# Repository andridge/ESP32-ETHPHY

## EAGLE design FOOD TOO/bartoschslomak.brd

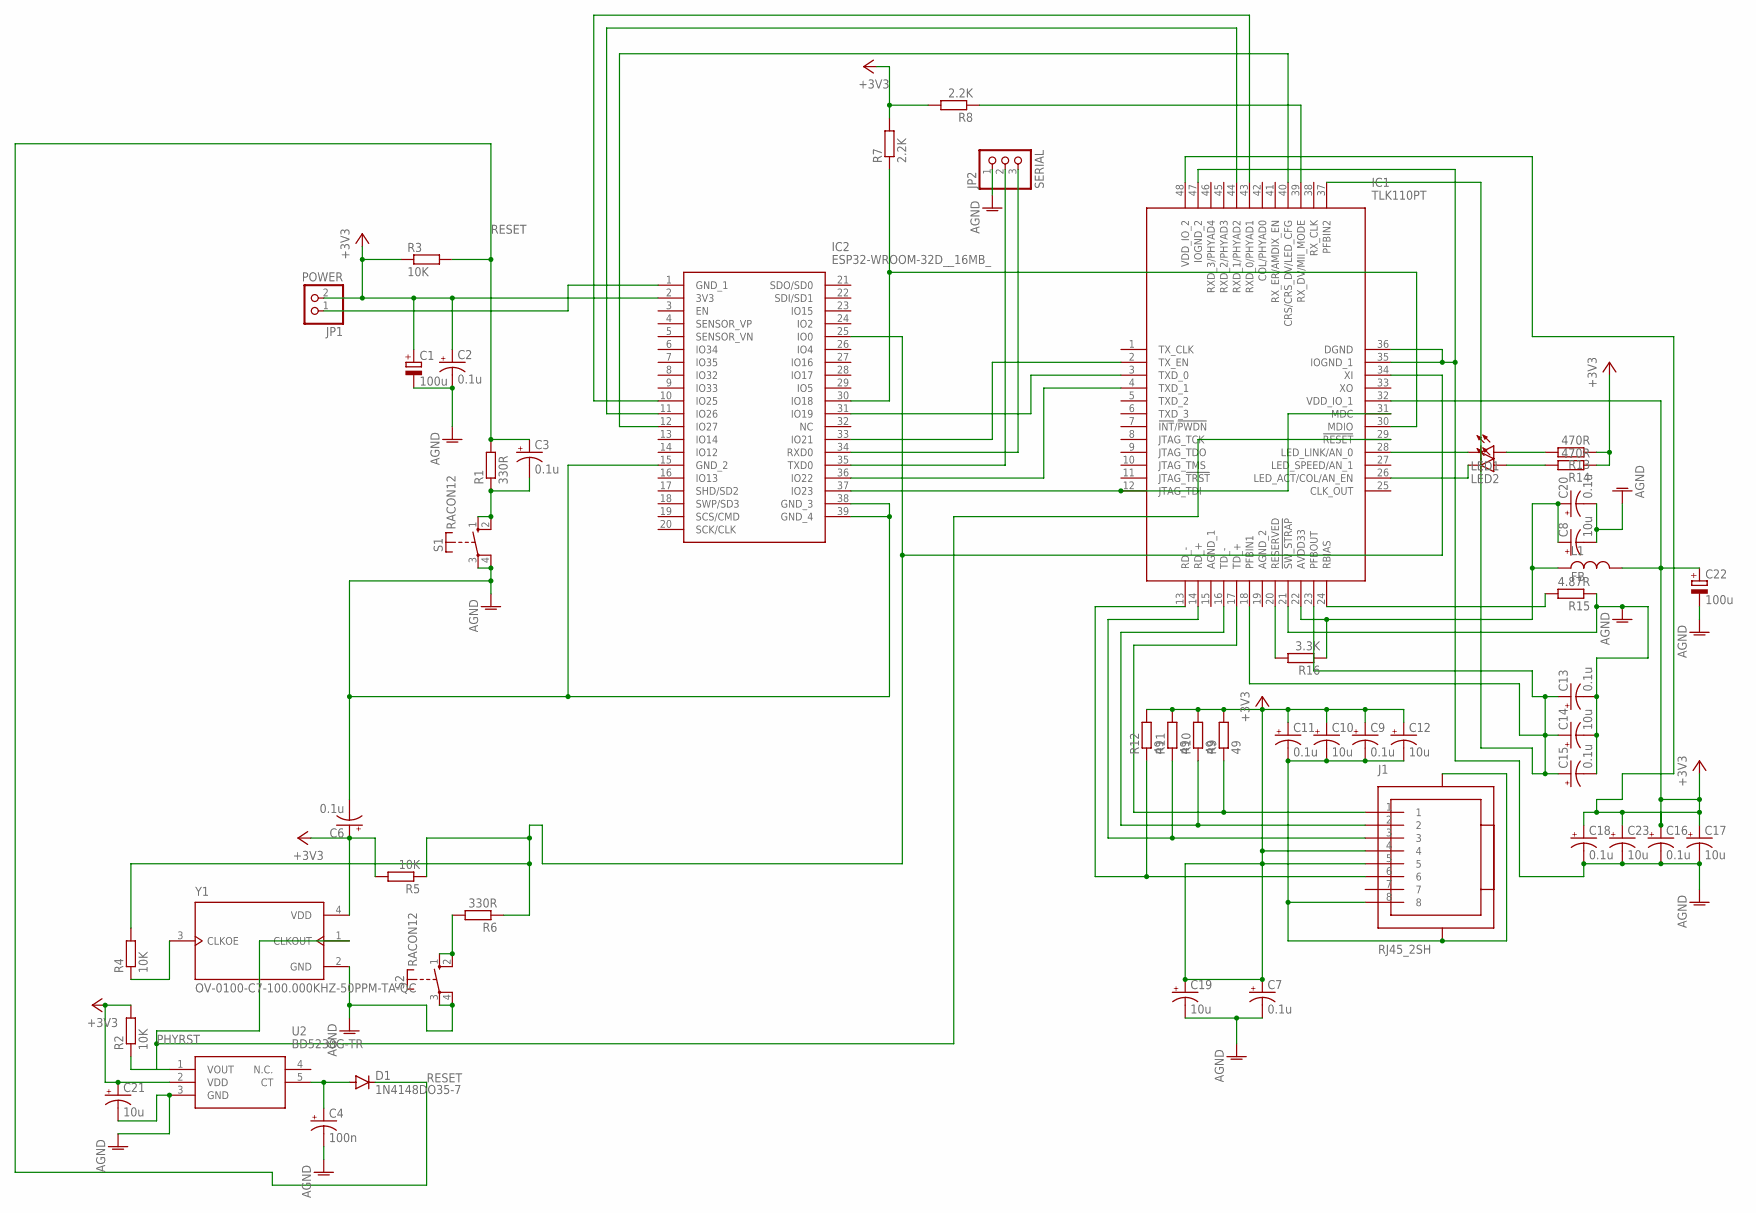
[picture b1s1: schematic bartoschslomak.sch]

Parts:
C1, C22: 100u; TT2D7
C2, C3, C6, C7, C9, C11, C13, C15, C16, C18, C20: 0.1u; A/3216-18R
C4: 100n; A/3216-18R
C8, C10, C12, C14, C17, C19, C21, C23: 10u; A/3216-18R
D1: 1N4148DO35-7; DO35-7
IC1: TLK110PT; QFP50P900X900X160-48N
IC2: ESP32-WROOM-32D__16MB_; ESP32WROOM32D16MB
J1: RJ45_2SH; RJ45_LP_RA_SMT
JP1: POWER; 1X02
JP2: SERIAL; 1X03
LED1, LED2: LED; SMARTLED-TTW
R1, R6: 330R; R01005
R2, R3, R4, R5: 10K; R01005
R7, R8: 2.2K; R01005
R9, R10, R11, R12: 49; R01005
R13, R14: 470R; R01005
R15: 4.87R; R01005
R16: 3.3K; R01005
S1, S2: RACON12
U2: BD5230G-TR; SOT95P280X125-5N
Y1: OV-0100-C7-100.000KHZ-50PPM-TA-QC; OSC_OV-0100-C7-100.000KHZ-50PPM-TA-QC

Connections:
+3V1: C13.+, C14.+, C15.+, IC1.18 (PFBIN1), IC1.23 (PFBOUT), IC1.37 (PFBIN2)
+3V3: C1.+, C2.+, C6.+, C7.+, C9.+, C10.+, C11.+, C12.+, C16.+, C17.+, C18.+, C19.+, C21.+, C22.+, C23.+, IC1.32 (VDD_IO_1), IC1.48 (VDD_IO_2), IC2.2 (3V3), J1.4, J1.5, JP1.2, R2.2, R3.1, R5.2, R7.2, R8.2, R9.2, R10.2, R11.2, R12.2, R13.1, R14.1, U2.2 (VDD), Y1.4 (VDD)
AGND: C1.-, C2.-, C4.-, C6.-, C7.-, C8.-, C13.-, C14.-, C15.-, C16.-, C17.-, C18.-, C19.-, C20.-, C21.-, C22.-, C23.-, IC1.21 (!SW_STRAP), IC1.35 (IOGND_1), IC1.36 (DGND), IC1.47 (IOGND_2), IC2.15 (GND_2), IC2.38 (GND_3), IC2.39 (GND_4), JP2.1, R15.1, S1.3, S1.4, S2.3, S2.4, U2.3 (GND), Y1.2 (GND)
unnamed: IC2.1 (GND_1), JP1.1
unnamed: R4.1, Y1.3 (CLKOE)
unnamed: C3.-, R1.1, S1.1 (S), S1.2 (S)
unnamed: IC1.34 (XI), IC2.25 (IO0), R4.2, R5.1, R6.1
unnamed: IC2.34 (RXD0), JP2.3
unnamed: R6.2, S2.1 (S), S2.2 (S)
unnamed: IC2.35 (TXD0), JP2.2
unnamed: C4.+, D1.A, U2.5 (CT)
unnamed: IC1.12 (JTAG_TDI), IC1.31 (MDC), IC2.37 (IO23)
unnamed: IC1.43 (RXD_0/PHYAD1), IC2.10 (IO25)
unnamed: IC1.44 (RXD_1/PHYAD2), IC2.11 (IO26)
unnamed: IC1.40 (CRS/CRS_DV/LED_CFG), IC2.12 (IO27)
unnamed: IC1.4 (TXD_1), IC2.36 (IO22)
unnamed: IC1.2 (TX_EN), IC2.33 (IO21)
unnamed: IC1.3 (TXD_0), IC2.31 (IO19)
unnamed: IC1.30 (MDIO), IC2.30 (IO18), R7.1
unnamed: IC1.24 (RBIAS), R15.2
unnamed: IC1.39 (RX_DV/MII_MODE), R8.1
unnamed: C9.-, C10.-, C11.-, C12.-, J1.8, J1.S$1 (SHIELD), J1.S$2 (SHIELD)
unnamed: IC1.20 (RESERVED), R16.2
unnamed: IC1.17 (TD_+), J1.1, R9.1
unnamed: IC1.16 (TD_-), J1.2, R10.1
unnamed: IC1.14 (RD_+), J1.3, R11.1
unnamed: IC1.13 (RD_-), J1.6, R12.1
unnamed: C8.+, C20.+, IC1.22 (AVDD33), R16.1
unnamed: IC1.26 (LED_ACT/COL/AN_EN), LED2.C@1 (C)
unnamed: IC1.28 (LED_LINK/AN_0), LED1.C@1 (C)
unnamed: LED1.A@1 (A), R13.2
unnamed: LED2.A@1 (A), R14.2
PHYRST: IC1.29 (!RESET), R2.1, U2.1 (VOUT), Y1.1 (CLKOUT)
RESET: C3.+, D1.C, R1.2, R3.2

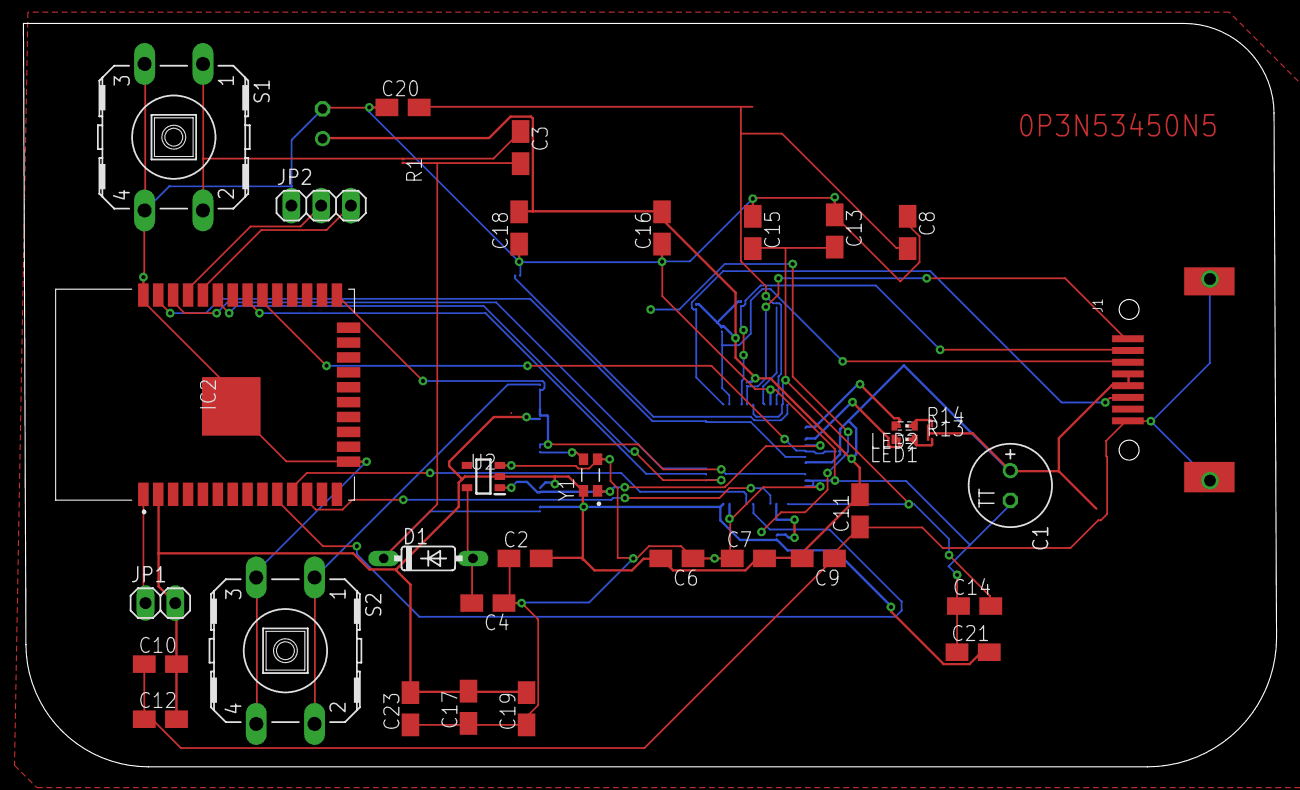
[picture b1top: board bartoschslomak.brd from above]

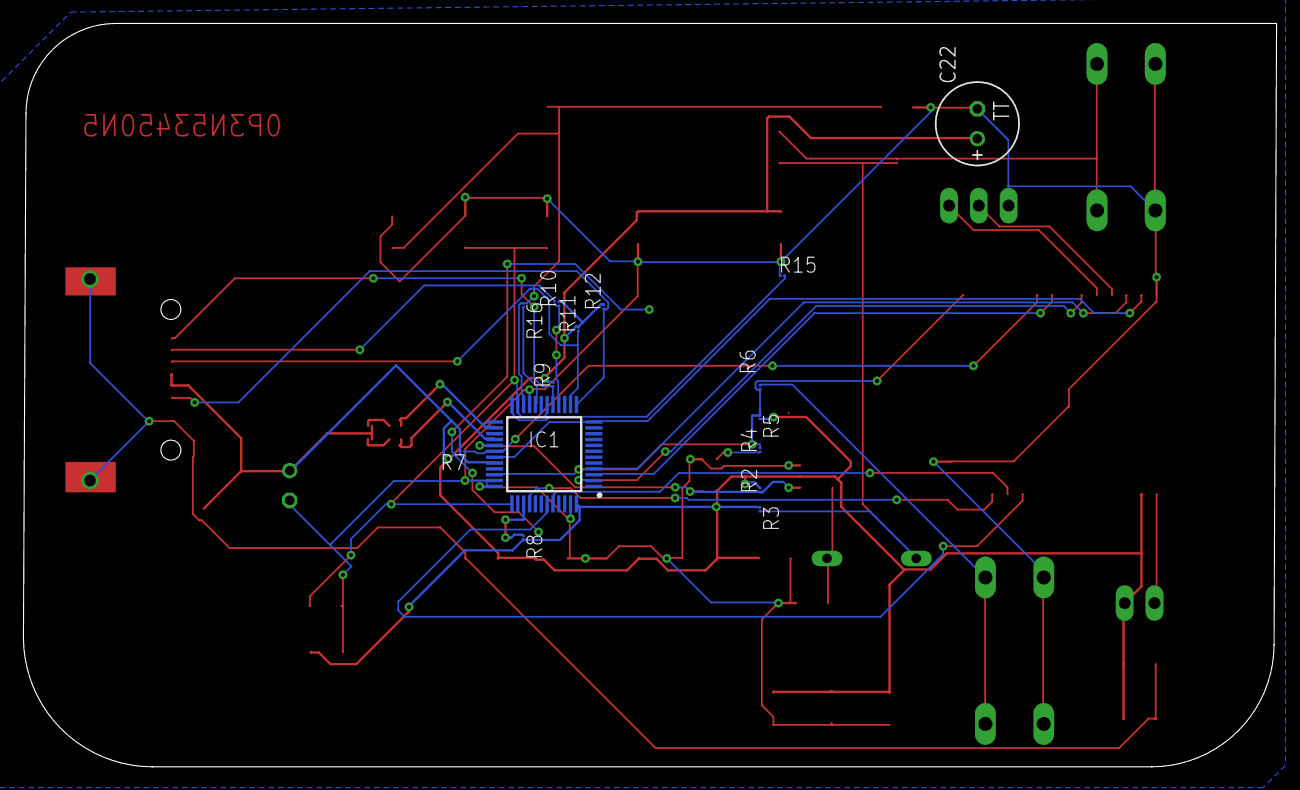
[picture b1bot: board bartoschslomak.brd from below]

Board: 2 copper layers, 106.9 x 63.4 mm, 50 parts (15 on the bottom side), 34 nets.

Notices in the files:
parts and their libraries:
TL-WR703N: Copyright © 2012, Michel Stempin, All rights reserved
Licenced under Creative Commons CC BY-SA 3.0 license.
